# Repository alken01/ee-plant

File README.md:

# ee-plant 🌱
## EE5/IoT02

### Intro
If you do not have the time to take care of your plants or when you are away from home for a few days, the ee-plant can help you! The system can look after different plant species, from common house plants to exotic ones. Specialised algorithms are designed with that in mind, tailored for every kind. 

The ee-plant comes with an Android app that updates the user about the plant. Is it too cold? The temperature goes up! Is it too dry? The system will water the plant. If the reservoir's water level is low, the app will notify the user.

Of course, you can take matters into your own hands and adjust every command accordingly.

### Sensors
The following sensors monitor the system 24/7:

- the soil moisture
- the air humidity
- temperature
- light intake

### Actuators
The following actuators regulate and control the system:

- a heater warms up the air
- a fan cools down the environment and regulates the humidity
- a spray machine, connected to a servo motor, sprays water and increase the humidity
- the water reservoir, attached with a pump and a servo motor, waters the soil

### Finally
The system's exterior is made out of a plexiglass box, MDF and 3D printed components. A power bank supplies the system with 5V. The ESP32 communicates with the database in the server through its Wi-Fi module. Data from the sensors is saved in these databases. It is then made available to the user via the app in form of graphs over time

> With the ee-plant everything is about nature and comfort.

## Sprints

### Sprint 1
In sprint 1 we worked mainly on the system's sensors.
The following user stories were closed:

- As a user I want to organise the data in databases
- As a user I want to know the temperature
- As a user I want to know the humidity and the moisture
- As a user I want to know the water level of the reservoir
- As a user I want to know if the plant is in light

[Video Sprint 1](https://kuleuven.mediaspace.kaltura.com/media/EE5+Team+IoT+2+-+Sprint+1/1_wgv9ouep)

### Sprint 2

The following user stories were closed:

- As a user I want to know the water level of the reservoir
- As a user I want to know if the plant is in light
- As a user I want to know the humidity and the moisture
- As a user I want to know the temperature
- As a user I want to organise the data in databases
- As a user I want a nice exterior design/case

Progress was made in the following:

- As a user I want to have a custom REST API
- As a user I want an Android App to control the device
- As a user I want to control the lighting

[Video Sprint 2](https://kuleuven.mediaspace.kaltura.com/media/EE5+Team+IoT+2+-+Sprint+2/1_kdvxv84o)

### Sprint 3

The following user stories were closed:

- As a user I want an iOS app to control the device
- As a user I want to have a smart device
- As a user I want everything to fit in the same case
- As a user I want to water the plant
- As a user I want to have web connectivity
- As a user I want to have as minimal wiring as possible (PCB)

[Video Sprint 3](https://kuleuven.mediaspace.kaltura.com/media/ee-plant+sprint+3+bew/1_60p68z9a)

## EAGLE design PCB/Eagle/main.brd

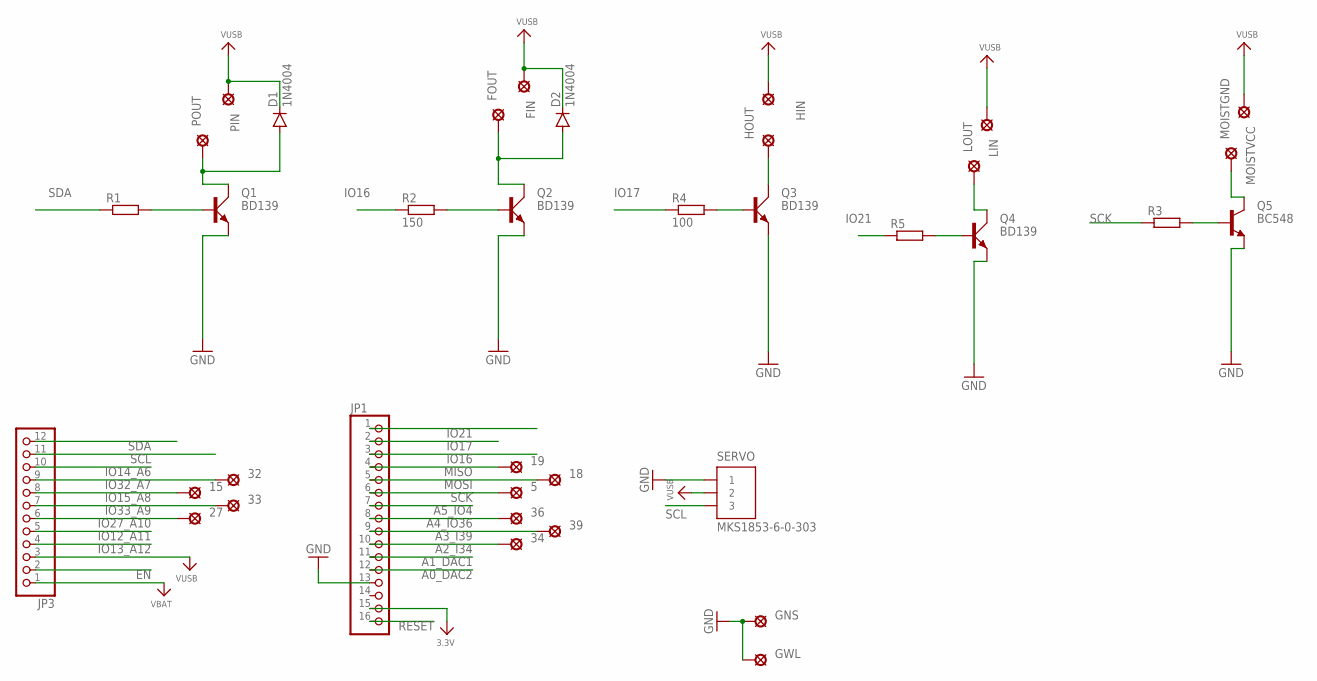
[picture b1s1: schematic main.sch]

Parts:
5, 15, 18, 19, 27, 32, 33, 34, 36, 39: SE13
D1, D2: 1N4004; DO41-10
FIN: SE13
FOUT: SE13
GNS: SE13
GWL: SE13
HIN: SE13
HOUT: SE13
JP1: HEADER-1X16_MIN; 1X16_ROUND_MIN
JP3: HEADER-1X12_MIN; 1X12_ROUND_MIN
LIN: SE13
LOUT: SE13
MOISTGND: SE13
MOISTVCC: SE13
PIN: SE13
POUT: SE13
Q1, Q2, Q3, Q4: BD139; TO126AV
Q5: BC548; TO92-EBC
R1, R3, R5: R-EU_R0805; R0805
R2: 150; R0805
R4: 100; R0805
SERVO: MKS1853-6-0-303

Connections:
3.3V: JP1.15
A0_DAC2: JP1.12
A1_DAC1: JP1.11
A2_I34: 34.MP, JP1.10
A3_I39: 39.MP, JP1.9
A4_IO36: 36.MP, JP1.8
A5_IO4: JP1.7
EN: JP3.2
GND: GNS.MP, GWL.MP, JP1.13, Q1.E, Q2.E, Q3.E, Q4.E, Q5.E, SERVO.1
IO12_A11: JP3.5
IO13_A12: JP3.4
IO14_A6: JP3.10
IO15_A8: 15.MP, JP3.8
IO16: JP1.3, R2.1
IO17: JP1.2, R4.1
IO21: JP1.1, R5.1
IO27_A10: 27.MP, JP3.6
IO32_A7: 32.MP, JP3.9
IO33_A9: 33.MP, JP3.7
MISO: 19.MP, JP1.4
MOSI: 18.MP, JP1.5
unnamed: Q4.B, R5.2
unnamed: Q3.B, R4.2
unnamed: LOUT.MP, Q4.C
unnamed: HOUT.MP, Q3.C
unnamed: D2.A, FOUT.MP, Q2.C
unnamed: Q2.B, R2.2
unnamed: D1.A, POUT.MP, Q1.C
unnamed: Q1.B, R1.2
unnamed: Q5.B, R3.2
unnamed: MOISTGND.MP, Q5.C
RESET: JP1.16
SCK: 5.MP, JP1.6, R3.1
SCL: JP3.11, SERVO.3
SDA: JP3.12, R1.1
VBAT: JP3.1
VBUS: D1.C, D2.C, FIN.MP, HIN.MP, JP3.3, LIN.MP, MOISTVCC.MP, PIN.MP, SERVO.2

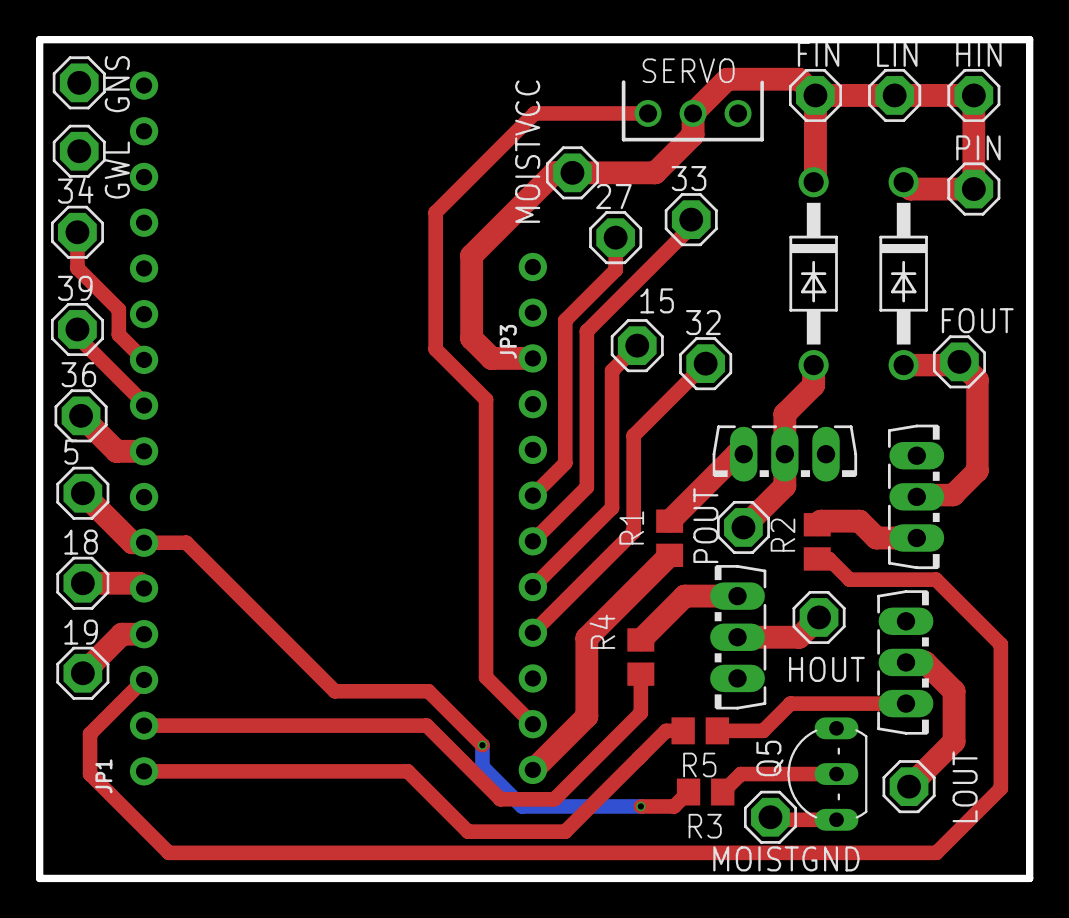
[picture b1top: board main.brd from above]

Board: 2 copper layers, 55.0 x 46.6 mm, 37 parts (0 on the bottom side), 27 nets.

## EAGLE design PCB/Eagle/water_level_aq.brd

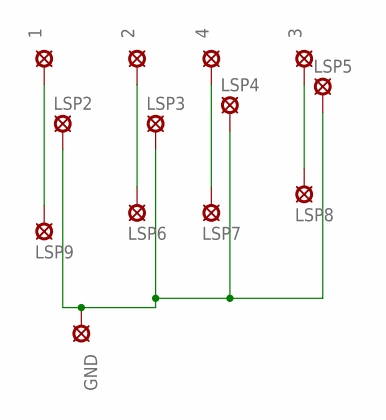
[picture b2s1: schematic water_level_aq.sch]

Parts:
1, 2, 3, 4: SE13
GND: SE13
LSP2, LSP3, LSP4, LSP5, LSP6, LSP7, LSP8, LSP9: MCS10B

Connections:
unnamed: 1.MP, LSP9.MP
unnamed: GND.MP, LSP2.MP, LSP3.MP, LSP4.MP, LSP5.MP
unnamed: 2.MP, LSP6.MP
unnamed: 4.MP, LSP7.MP
unnamed: 3.MP, LSP8.MP

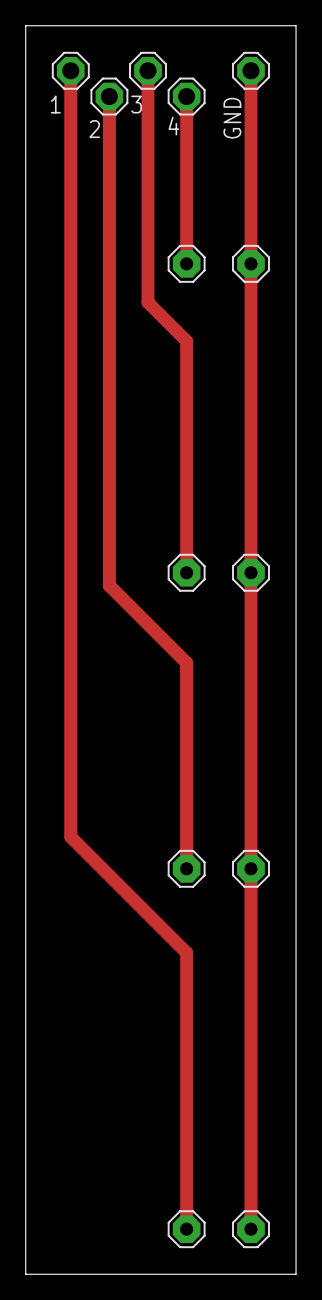
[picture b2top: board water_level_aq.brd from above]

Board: 2 copper layers, 21.0 x 97.0 mm, 13 parts (0 on the bottom side), 5 nets.

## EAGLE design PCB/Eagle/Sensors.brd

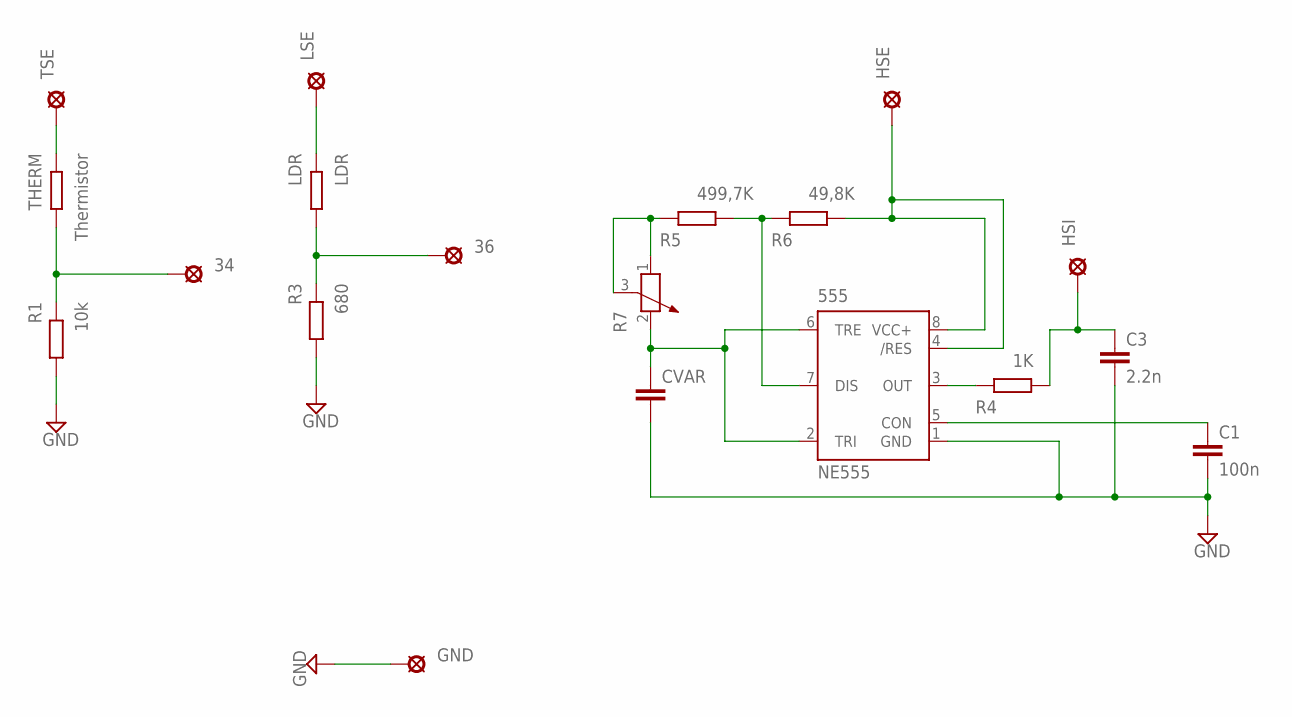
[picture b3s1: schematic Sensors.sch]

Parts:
34: SE13
36: 36; SE13
555: NE555; DIL-08
C1: 100n; C0805
C3: 2.2n; C0805
CVAR: C-EU050-025X075; C050-025X075
GND: SE13
HSE: SE13
HSI: SE13
LDR: LDR; WEERSTAND
LSE: SE13
R1: 10k; R0805
R3: 680; R0805
R4: 1K; R0805
R5: 499,7K; R0805
R6: 49,8K; R0805
R7: POTENTIOMETER_PT-10; PT-10
THERM: Thermistor; WEERSTAND
TSE: SE13

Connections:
34: 34.MP, R1.1, THERM.P$2
36: 36.MP, LDR.P$2, R3.1
GND: 555.1 (GND), C1.2, C3.2, CVAR.2, GND.MP, R1.2, R3.2
unnamed: THERM.P$1, TSE.MP
unnamed: LDR.P$1, LSE.MP
unnamed: 555.5 (CON), C1.1
unnamed: C3.1, HSI.MP, R4.2
unnamed: 555.3 (OUT), R4.1
unnamed: 555.4 (/RES), 555.8 (VCC+), HSE.MP, R6.2
unnamed: 555.2 (TRI), 555.6 (TRE), CVAR.1, R7.2
unnamed: R5.1, R7.1, R7.3
unnamed: 555.7 (DIS), R5.2, R6.1

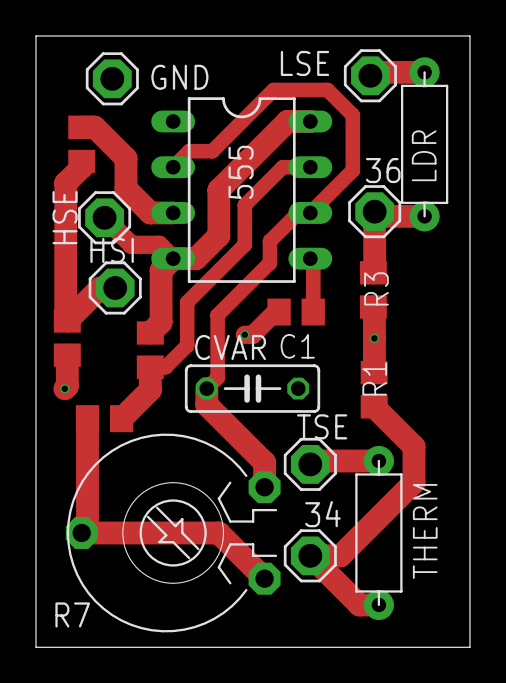
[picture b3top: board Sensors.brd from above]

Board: 2 copper layers, 24.1 x 34.0 mm, 19 parts (0 on the bottom side), 12 nets.

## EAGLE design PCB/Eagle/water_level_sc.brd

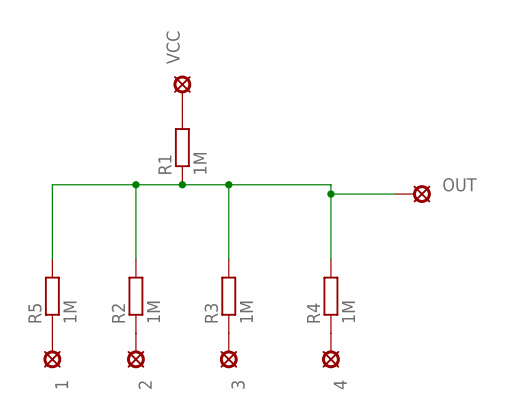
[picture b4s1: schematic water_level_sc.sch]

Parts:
1, 2, 3, 4: SE13
OUT: SE13
R1, R2, R3, R4, R5: 1M; R0805
VCC: SE13

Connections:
unnamed: 4.MP, R4.1
unnamed: 3.MP, R3.1
unnamed: 2.MP, R2.1
unnamed: 1.MP, R5.1
unnamed: R1.2, VCC.MP
unnamed: OUT.MP, R1.1, R2.2, R3.2, R4.2, R5.2

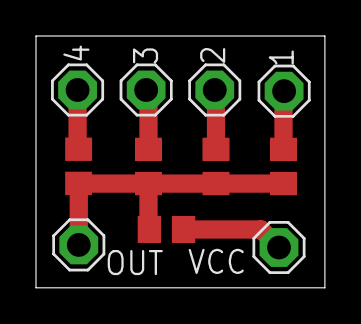
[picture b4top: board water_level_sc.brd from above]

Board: 2 copper layers, 16.1 x 14.0 mm, 11 parts (0 on the bottom side), 6 nets.

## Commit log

2022-02-23 add README
2022-02-24 Created the android app folder
2022-02-24 no message
2022-02-24 Deleted .idea/.gitignore, .idea/.name, .idea/gradle.xml, .idea/misc.xml, .idea/vcs.xml
2022-02-26 Add README.md
2022-02-27 test push
2022-03-01 database test
2022-03-06 Added Logo
2022-03-08 Test
2022-03-08 Add more c
2022-03-08 Added a header file
2022-03-08 Made folders
2022-03-08 Made updates
2022-03-08 Add esp-idf
2022-03-08 Deleted .idea/.gitignore, .idea/a21iot02.iml, .idea/misc.xml, .idea/modules.xml, .idea/vcs.xml
2022-03-08 Deleted .gitignore
2022-03-10 Added sample project
2022-03-14 Deleted cmake-build-debug/CMakeFiles/clion-log.txt, .idea/a21iot02.iml, .idea/misc.xml, .idea/modules.xml, .idea/vcs.xml, .idea/workspace.xml
2022-03-14 Updated sensor
2022-03-14 Extra
2022-03-29 Update: add sample project
2022-03-30 PWM working
2022-03-31 wifi 1.0
2022-03-31 added h-file
2022-03-31 update wifi
2022-04-04 add certificate to main
2022-04-10 water pump and water level sensing
2022-04-10 water pump and water level sensing V2
2022-04-10 Remove cmakecache.txt in build/bootloader and rerun.
2022-04-10 -wifi.c- line 115 in comment --> this was causing error
2022-04-11 Only ESP32
2022-04-12 water_pump.c DONE
2022-04-12 water_pump.c fine-tuning
2022-04-12 all readings complete. TODO: fill in trigger values. water_level: OK soil moisture: OK POMP goes on when SOIL DRY AND WATER NOT LOW
2022-04-21 insert air humidity c file
2022-04-21 Make air humidity file a callable file and not its own function, remove the app_main entry point
2022-04-21 sending data to database from esp works
2022-04-21 add stop_humidity as an exit point for the humidity sensor
2022-04-21 Deleted useless code in HTTPS REQUEST
2022-04-21 add Air_Humidity.h
2022-04-21 change location of Air_Humidity.h
2022-04-28 Added iOS app and the laravel code
2022-04-28 images
2022-04-28 image
2022-04-28 readme
2022-05-12 Added PHP Files
2022-05-12 Added some extra files
2022-05-12 Changed the logo to greeeeeen
2022-05-21 Added C Code
2022-06-01 iOS App
2022-06-01 Renamed to App
2022-06-01 Updated PHP files
2022-06-01 poster
2022-06-01 Added wiki and poster
2022-06-01 updated links
2022-06-01 deleted build
2022-06-01 Re index done

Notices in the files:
parts and their libraries:
microbuilder: This work is placed in the public domain, and may be freely used for commercial and non-commercial work with the following conditions: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
